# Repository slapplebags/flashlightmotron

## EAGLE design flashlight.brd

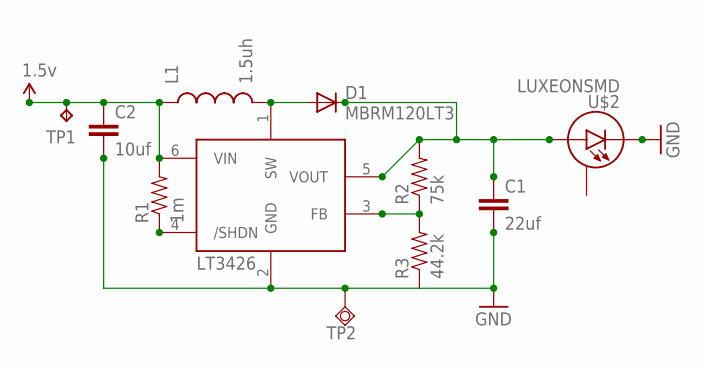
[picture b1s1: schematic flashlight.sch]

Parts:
C1: 22uf; 0805
C2: 10uf; 0805
D1: MBRM120LT3; SOD80C
L1: 1.5uh; 1007
R1: 1m; 0805
R2: 75k; 0805
R3: 44.2k; 0805
TP1: TPTP20R; TP20R
TP2: TPSQPAD1-13; P1-13
U$1: LT3426; SOT23-6
U$2: LUXEONSMD; LUXEON

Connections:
GND: C1.2, C2.2, R3.1, TP2.TP, U$1.2 (GND), U$2.C
unnamed: D1.A, L1.2, U$1.1 (SW)
unnamed: R1.1, U$1.4 (/SHDN)
unnamed: R2.1, R3.2, U$1.3 (FB)
unnamed: C1.1, D1.C, R2.2, U$1.5 (VOUT), U$2.A
VCC: C2.1, L1.1, R1.2, TP1.TP, U$1.6 (VIN)

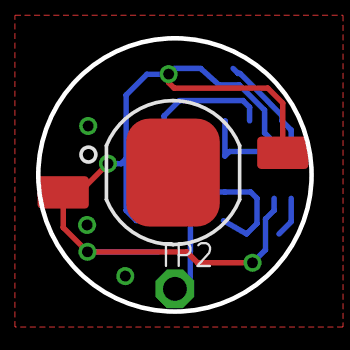
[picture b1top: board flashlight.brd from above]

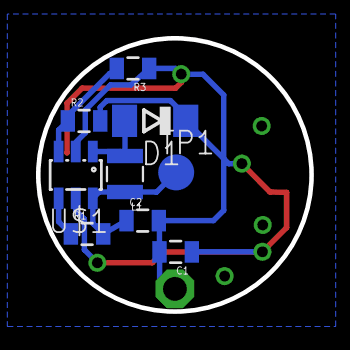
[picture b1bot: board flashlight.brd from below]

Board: 2 copper layers, 15.2 x 15.2 mm, 11 parts (9 on the bottom side), 6 nets.

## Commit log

2015-04-26 :boom::camel: Added .gitattributes & .gitignore files
2015-04-26 Fixed routing issues

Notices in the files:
parts and their libraries:
SparkFun-Passives: Licensing: Creative Commons ShareAlike 4.0 International - https://creativecommons.org/licenses/by-sa/4.0
